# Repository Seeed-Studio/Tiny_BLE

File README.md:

Tiny BLE
==========

The Tiny BLE is a Bluetooth Low Energy development board designed with low energy consumption and small size in mind. It's integrated with current measurement feature to provide real time energy consumption data, which is essential for developers to optimize software to design long battery life devices. It supports ARM mbed cloud-based IDE with an handy C/C++ SDK and a large number of open source libraries, which makes prototyping and development extremely easy. Further, to keep it small, we use modular design to enable it divide into two parts - CMSIS DAP interface part and BLE part.

----
### CMSIS DAP Interface Part
The interface is very powerful to provide features :

+ Drag-n-drop programming
+ CMSIS DAP debug
+ USB Virtual serial port
+ Current measurement
+ Battery charging

To enable the current measurement feature, just set the baud rate of the USB virtual serial port to 4000000+, then the current data of the BLE part will be sent through the virtual serial port. To make data easier to use, we create a cross platform tool - BLE Smurfs Monitor to make it visual.

+ [Tiny BLE Monitor for Windows](http://tangram.qiniudn.com/ble_smurfs_monitor_v0.1.exe)
+ [Tiny BLE Monitor for Linux/Mac OS](https://github.com/Seeed-Studio/Tiny_BLE/tree/master/utils), additional requirements: pyqtgraph, pyside

----

### BLE part

+ Nordic nRF51822 with BLE and ARM Cortex M0
+ MPU6050, 3d accelerometer and 3d gyroscope
+ RGB LED
+ Battery Connector & Battery Voltage Measurement
+ all 4 I/Os can be used as analog input, digital input/output, i2c, spi or uart

The BLE part is built on the Nordic nRF51822 with Bluetooth Low Energy 2.4GHz multiprotocol radio and a 32 bit ARM Cortex-M0 core running 16MHz.
MPU6050, a 6 DOF with 3D accelerometer and 3D gyroscope, is integrated to provide motion detect feature. The Digital Motion Processor (DMP) of the MPU6050 provide several features (such as gesture detect, pedometer, calibrating gyro data) which
can reduce running time of the nRF51822 to get a long battery life. It also integrates battery connector and battery voltage measurement circuit for you.
We custom a bootloader for the BLE Smurfs to enable Firmware-Over-The-Air feature. when the BLE Smurfs is divided into two parts, we can still update the firmware of the nRF51822 through FOTA

Have fun!

----

This software in this repository is written by [Seeedstudio](http://seeed.cc)<br>
and is licensed under [The Apache License V2.0](http://www.apache.org/licenses/LICENSE-2.0).

Contributing to this software is warmly welcomed. You can do this basically by<br>
[forking](https://help.github.com/articles/fork-a-repo), committing modifications and then [pulling requests](https://help.github.com/articles/using-pull-requests) (follow the links above<br>
for operating guide). Adding change log and your contact into file header is encouraged.<br>
Thanks for your contribution.

Seeed Studio is an open hardware facilitation company based in Shenzhen, China. <br>
Benefiting from local manufacture power and convenient global logistic system, <br>
we integrate resources to serve new era of innovation. Seeed also works with <br>
global distributors and partners to push open hardware movement.<br>

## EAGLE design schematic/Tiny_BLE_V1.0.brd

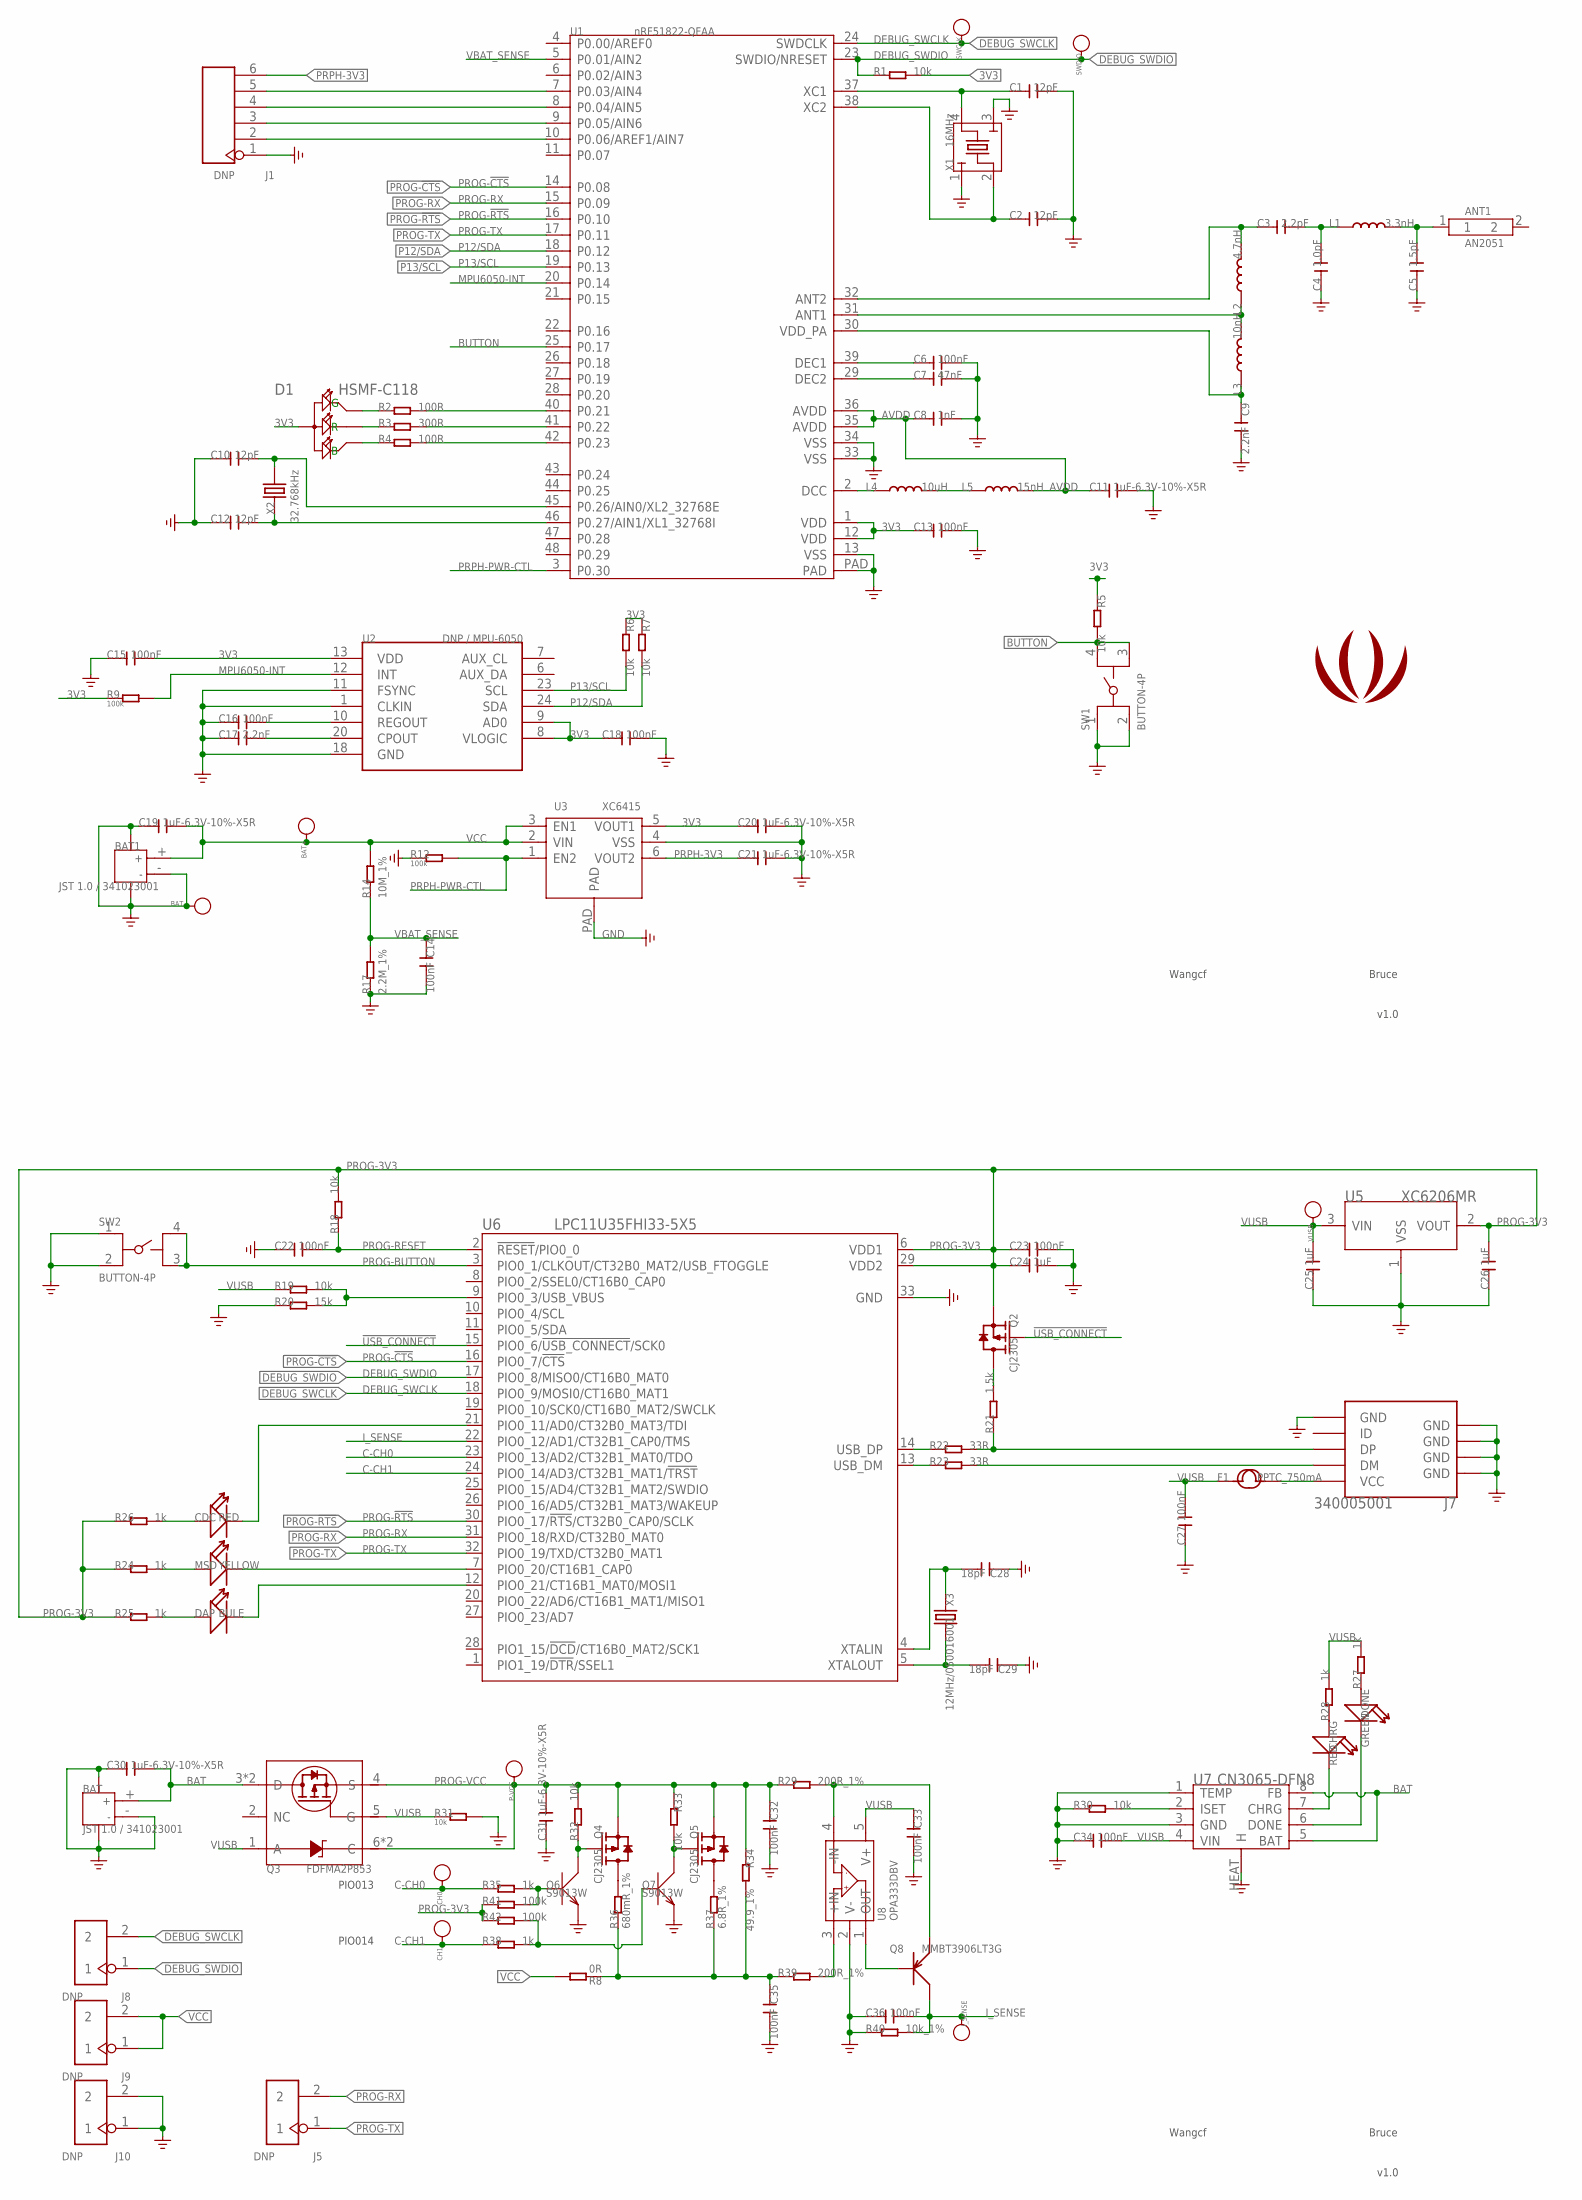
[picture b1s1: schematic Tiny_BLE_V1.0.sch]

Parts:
ANT1: AN2051; 2P-SMD-L5.05*W.02*H1.07MM
BAT, BAT1: JST 1.0 / 341023001; JST-SMD-2P-1.0-90D
BAT+: BAT+; PAD_4080
BAT-: BAT-; PAD_4080
C1, C2, C10, C12: 12pF; C0402
C3: 2.2pF; C0402
C4: 1.0pF; C0402
C5: 1.5pF; C0402
C6, C13, C14, C15, C16, C18, C22, C23, C27, C32, C33, C34, C35, C36: 100nF; C0402
C7: 47nF; C0402
C8: 1nF; C0402
C9, C17: 2.2nF; C0402
C11, C19, C20, C21, C30, C31: 1uF-6.3V-10%-X5R; C0402
C24, C25, C26: 1uF; C0402
C28, C29: 18pF; C0402
CDC: RED; LED-0603
CH0: CH0; TP_4545
CH1: CH1; TP_4545
CHRG: RED; LED-0603
D1: HSMF-C118; LED-4P-1210-3.0X2.54
DAP: BULE; LED-0603
DONE: GREEN; LED-0603
F1: PPTC_750mA; F1206
I_SENSE: I_SENSE; TP_4545
J1: DNP; 6P-2.54-60/35MIL
J5, J8, J9, J10: DNP; 2P-2.54-65/35MIL
J7: 340005001; MICRO-USB
L1: 3.3nH; L0402
L2: 4.7nH; L0402
L3: 10nH; L0402
L4: 10uH; L0603
L5: 15nH; L0402
MSD: YELLOW; LED-0603
P-VCC: P_VCC; TP_4545
Q2, Q4, Q5: CJ2305; SOT23
Q3: FDFMA2P853; 6P-SMD-W/-HEAT
Q6, Q7: S9013W; SOT323
Q8: MMBT3906LT3G; SOT23
R1, R5, R6, R7, R18, R19, R30, R31, R32, R33: 10k; R0402
R2, R4: 100R; R0402
R3: 300R; R0402
R8: 0R; R0603
R9, R12, R41, R42: 100k; R0402
R14: 10M_1%; R0402
R17: 2.2M_1%; R0402
R20: 15k; R0402
R21: 1.5k; R0402
R22, R23: 33R; R0402
R24, R25, R26, R27, R28, R35, R38: 1k; R0402
R29, R39: 200R_1%; R0402
R34: 49.9_1%; R0603
R36: 680mR_1%; R0603
R37: 6.8R_1%; R0603
R40: 10k_1%; R0402
SW1, SW2: BUTTON-4P; 4P-SMD-L4.45*W3.22*H2.5MM
SWCLK: SWDCLK; PAD_4080
SWDIO: SWDIO; PAD_4080
U1: nRF51822-QFAA; QFN48-6X6MM
U2: DNP / MPU-6050; QFN24
U3: XC6415; USP-6C
U5: XC6206MR; SOT23
U6: LPC11U35FHI33-5X5; HVQFN33
U7: CN3065-DFN8; DFN8
U8: OPA333DBV; SOT23-5
U$59: LOGO-SEEEDSTUDIO-SMALL-SILK; SMALL_SEEED_LOGO
VUSB: VUSB; TP_4545
X1: 16MHz; 2520
X2: 32.768kHz; 2P-SMD-3.2X1.5
X3: 12MHz/050016001; 2P-SMD-5X3.2

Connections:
3V3: C13.1, C15.2, C18.1, C20.1, D1.1 (+), R1.2, R5.1, R6.1, R7.1, R9.1, U1.1 (VDD), U1.12 (VDD), U2.8 (VLOGIC), U2.9 (AD0), U2.13 (VDD), U3.5 (VOUT1)
!USB_CONNECT: Q2.1 (G), U6.15 (PIO0_6/!USB_CONNECT!/SCK0)
AVDD: C8.1, C11.1, L5.2, U1.35 (AVDD), U1.36 (AVDD)
BAT: BAT.+ (1), C30.2, Q3.3 (D), Q3.P2 (D), U7.5 (BAT), U7.8 (FB)
BUTTON: R5.2, SW1.3, SW1.4, U1.25 (P0.17)
C-CH0: CH0.T, R35.1, U6.23 (PIO0_13/AD2/CT32B1_MAT0/TDO)
C-CH1: CH1.T, R38.1, U6.24 (PIO0_14/AD3/CT32B1_MAT1/!TRST!)
CHRG: CHRG.-, U7.7 (CHRG)
CHRG-DONE: DONE.-, U7.6 (DONE)
DCC: L4.1, U1.2 (DCC)
DEBUG_SWCLK: J8.2, SWCLK.1, U1.24 (SWDCLK), U6.18 (PIO0_9/MOSI0/CT16B0_MAT1)
DEBUG_SWDIO: J8.1, R1.1, SWDIO.1, U1.23 (SWDIO/NRESET), U6.17 (PIO0_8/MISO0/CT16B0_MAT0)
GND: BAT.3, BAT.4, BAT.- (2), BAT1.3, BAT1.4, BAT1.- (2), BAT-.1, C1.2, C2.2, C4.1, C5.1, C6.2, C7.2, C8.2, C9.2, C10.1, C11.2, C12.1, C13.2, C14.2, C15.1, C16.1, C17.1, C18.2, C19.1, C20.2, C21.2, C22.1, C23.2, C24.2, C25.1, C26.1, C27.1, C28.1, C29.1, C30.1, C31.1, C32.2, C33.2, C34.1, C35.2, C36.1, J1.1, J7.5 (GND), J7.S1 (GND), J7.S2 (GND), J7.S3 (GND), J7.S4 (GND), J7.S5 (GND), J7.S6 (GND), J10.1, J10.2, Q6.2 (E), Q7.2 (E), R12.1, R17.1, R20.1, R30.1, R31.2, R40.1, SW1.1, SW1.2, SW2.1, SW2.2, U1.13 (VSS), U1.33 (VSS), U1.34 (VSS), U1.PAD, U2.1 (CLKIN), U2.11 (FSYNC), U2.18 (GND), U3.4 (VSS), U3.PAD, U5.1 (VSS), U6.33 (GND), U7.1 (TEMP), U7.3 (GND), U7.HEAT (H), U8.2 (V-), X1.1, X1.3
ISET: R30.2, U7.2 (ISET)
I_SENSE: C36.2, I_SENSE.T, Q8.3 (C), R40.2, U6.22 (PIO0_12/AD1/CT32B1_CAP0/TMS)
MPU6050-INT: R9.2, U1.20 (P0.14), U2.12 (INT)
unnamed: Q8.2 (E), R29.2, U8.4 (-IN)
unnamed: C29.2, U6.5 (XTALOUT), X3.2
unnamed: D1.3 (G), R2.1
unnamed: C28.2, U6.4 (XTALIN), X3.1
unnamed: D1.2 (R), R3.1
unnamed: R22.1, U6.14 (USB_DP)
unnamed: R23.1, U6.13 (USB_DM)
unnamed: J7.3 (DP), R21.1, R22.2
unnamed: Q4.1 (G), Q6.3 (C), R32.1
unnamed: J7.2 (DM), R23.2
unnamed: C10.2, U1.45 (P0.26/AIN0/XL2_32768E), X2.2
unnamed: C12.2, U1.46 (P0.27/AIN1/XL1_32768I), X2.1
unnamed: C1.1, U1.37 (XC1), X1.4
unnamed: C2.1, U1.38 (XC2), X1.2
unnamed: CDC.-, U6.21 (PIO0_11/AD0/CT32B0_MAT3/TDI)
unnamed: C16.2, U2.10 (REGOUT)
unnamed: C6.1, U1.39 (DEC1)
unnamed: C17.2, U2.20 (CPOUT)
unnamed: C7.1, U1.29 (DEC2)
unnamed: C3.1, L2.2, U1.32 (ANT2)
unnamed: L2.1, L3.2, U1.31 (ANT1)
unnamed: C9.1, L3.1, U1.30 (VDD_PA)
unnamed: C3.2, C4.2, L1.1
unnamed: ANT1.1, C5.2, L1.2
unnamed: L4.2, L5.1
unnamed: Q2.3 (D), R21.2
unnamed: F1.2, J7.1 (VCC)
unnamed: R19.2, R20.2, U6.9 (PIO0_3/USB_VBUS)
unnamed: CDC.+, R26.2
unnamed: DAP.+, R25.2
unnamed: MSD.+, R24.2
unnamed: MSD.-, U6.7 (PIO0_20/CT16B1_CAP0)
unnamed: DAP.-, U6.12 (PIO0_21/CT16B1_MAT0/MOSI1)
unnamed: D1.4 (B), R4.1
unnamed: Q8.1 (B), U8.1 (OUT)
unnamed: R39.2, U8.3 (+IN)
unnamed: Q5.3 (D), R37.2
unnamed: Q4.3 (D), R36.2
unnamed: Q6.1 (B), R35.2, R41.2
unnamed: Q5.1 (G), Q7.3 (C), R33.2
unnamed: Q7.1 (B), R38.2, R42.2
unnamed: DONE.+, R27.1
unnamed: CHRG.+, R28.1
unnamed: R2.2, U1.40 (P0.21)
unnamed: R3.2, U1.41 (P0.22)
unnamed: R4.2, U1.42 (P0.23)
unnamed: J1.2, U1.10 (P0.06/AREF1/AIN7)
unnamed: J1.3, U1.9 (P0.05/AIN6)
unnamed: J1.4, U1.8 (P0.04/AIN5)
unnamed: J1.5, U1.7 (P0.03/AIN4)
unnamed: C35.1, R8.1, R34.2, R36.1, R37.1, R39.1
P12/SDA: R7.2, U1.18 (P0.12), U2.24 (SDA)
P13/SCL: R6.2, U1.19 (P0.13), U2.23 (SCL)
PROG-3V3: C23.1, C24.1, C26.2, Q2.2 (S), R18.2, R24.1, R25.1, R26.1, R41.1, R42.1, U5.2 (VOUT), U6.6 (VDD1), U6.29 (VDD2)
PROG-!CTS: U1.14 (P0.08), U6.16 (PIO0_7/!CTS!)
PROG-!RTS: U1.16 (P0.10), U6.30 (PIO0_17/!RTS!/CT32B0_CAP0/SCLK)
PROG-BUTTON: SW2.3, SW2.4, U6.3 (PIO0_1/CLKOUT/CT32B0_MAT2/USB_FTOGGLE)
PROG-RESET: C22.2, R18.1, U6.2 (!RESET!/PIO0_0)
PROG-RX: J5.2, U1.15 (P0.09), U6.31 (PIO0_18/RXD/CT32B0_MAT0)
PROG-TX: J5.1, U1.17 (P0.11), U6.32 (PIO0_19/TXD/CT32B0_MAT1)
PROG-VCC: C31.2, C32.1, P-VCC.T, Q3.4 (S), Q3.6 (C), Q3.P1 (C), Q4.2 (S), Q5.2 (S), R29.1, R32.2, R33.1, R34.1
PRPH-3V3: C21.1, J1.6, U3.6 (VOUT2)
PRPH-PWR-CTL: R12.2, U1.3 (P0.30), U3.1 (EN2)
VBAT_SENSE: C14.1, R14.1, R17.2, U1.5 (P0.01/AIN2)
VCC: BAT1.+ (1), BAT+.1, C19.2, J9.1, J9.2, R8.2, R14.2, U3.2 (VIN), U3.3 (EN1)
VUSB: C25.2, C27.2, C33.1, C34.2, F1.1, Q3.1 (A), Q3.5 (G), R19.1, R27.2, R28.2, R31.1, U5.3 (VIN), U7.4 (VIN), U8.5 (V+), VUSB.T

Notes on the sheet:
Wangcf
PIO014
PIO013
Bruce
v1.0

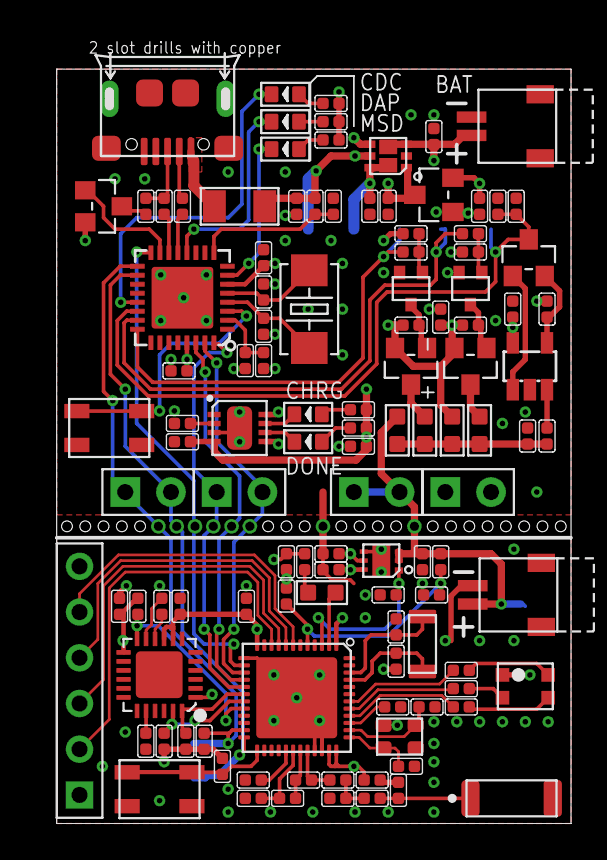
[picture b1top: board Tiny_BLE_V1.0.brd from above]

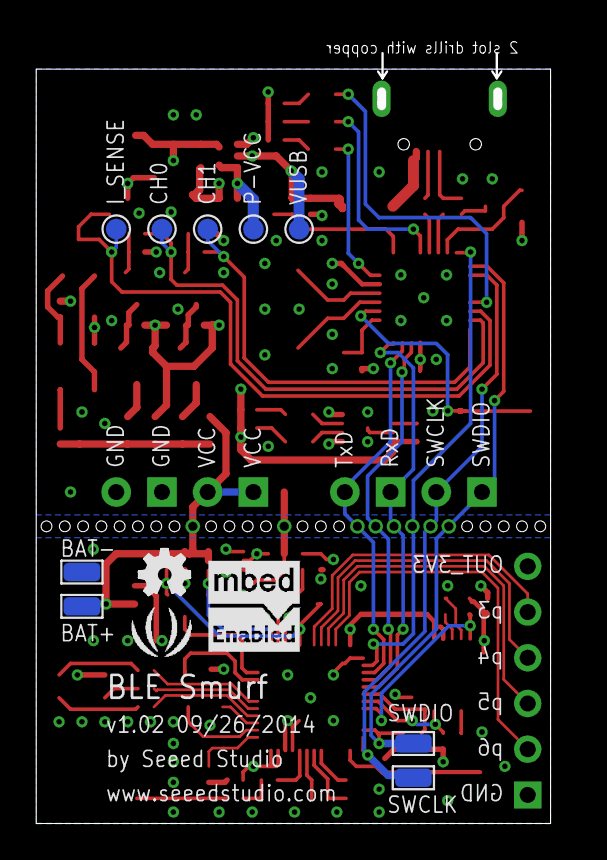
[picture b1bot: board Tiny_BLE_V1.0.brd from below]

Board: 4 copper layers, 28.6 x 42.8 mm, 124 parts (11 on the bottom side), 82 nets.

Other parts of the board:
U$30: OSHW_FILLX100_NOTEXT

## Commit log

2014-12-05 initial
2014-12-16 fix serial port info issue on linux
2014-12-19 add contents
2015-02-04 change name and add schematic
2015-02-07 add interface firmware
2015-03-05 Fix for OSX USB serial detection
2016-03-04 add ble sniffer application
2016-03-16 use numpy to improve performance
2024-10-08 Add sync_issues GitHub Action for workflows
2025-01-08 ci: add an action to automatically close stale issues and PRs
